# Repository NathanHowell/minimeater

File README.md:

# minimeater

A fan controller for a Big Green Egg Large. It is a single 3D-printed box that clips onto the egg's intake tube. It
meters air into the fire with a fan and a servo-driven flap to hold the pit at a setpoint between 150 and 325 °F.
It runs from one USB-C cable and talks to Home Assistant over MQTT.

> [!WARNING]
> **Status: design, not yet built.** The board, the enclosure and the firmware are complete enough to order and run in
> simulation, but no unit has been made or used on a real cook. Expect changes, and don't trust it with a fire yet.

## What it does

- **Holds the pit temperature.** A model-predictive controller plans the airflow half an hour ahead on a model of the
  egg, because the pit answers a change of air long after it is made. It treats overshoot as much worse than
  undershoot (a kamado can only be starved of air, not cooled) and continuously estimates what the model doesn't know:
  the fire, the weather and the food. It commands airflow; the fan and the flap are scheduled to deliver it. It
  recovers from an opened lid, tunes itself during a cook and resumes after a power cut.
- **Watches the food.** Four thermistor probe jacks. Any of them can be the pit probe (it is found automatically); the
  rest report temperature, rate of rise, an estimated finish time and stall detection, with high and low alarms.
- **Fits in with a smart home.** Home Assistant entities through MQTT discovery, over TLS 1.3 with a per-device key held
  in a secure element. Metrics go to any OpenTelemetry collector. WiFi is set up from the browser (Improv) or the
  serial console.
- **Needs nothing else.** One USB-C port powers it, flashes it and carries the console. No 12 V supply, no separate
  blower.

## Safety

This device controls a fire. A fault in the controller, the firmware or the setup can leave the fan running and the
pit far hotter than intended. Use it only on a cooker you would otherwise trust to be left alone, keep the cooker's
own vents set so that a fan running flat out is still safe, and don't leave a cook unattended until you have tested it
yourself. It comes with no warranty (see [License](#license)).

## How it is built

<p align="center"><sub>The board, 47.5 × 54 mm, four layers. It hangs parts-down in the box, so the silk side is the face you see with the case open.</sub></p>

| | Where | Docs |
|---|---|---|
| **Board** | `hw/`: KiCad 10, four layers, assembled by JLCPCB. An ESP32-C6, the probe front end, USB-C power, the fan and servo drivers, an ATECC608B for the device key | [ADRs](docs/adr/), [ICD](docs/icd.md), [ordering](docs/ordering.md) |
| **Enclosure** | `src/minimeater/mech/`: build123d, printed in MJF nylon (duct, hood, pan) with a few CNC parts (flap, crank, coupler, rod) | [mech](docs/mech.md), [JLC3DP notes](docs/jlc3dp.md), [CFD](docs/cfd.md) |
| **Firmware** | `fw/`: Rust, `no_std`, embassy. `minimeater-core` (control, food estimator, probe conversion), `minimeater-app` (the application, generic over the board), `minimeater-fw` (the ESP32-C6 binding) | [MQTT protocol](docs/protocol.md), [telemetry](docs/telemetry.md), [provisioning](docs/provisioning.md) |
| **Digital twin** | `fw/minimeater-sim` and `fw/minimeater-twin`: the real application tasks on a virtual clock against a simulated board and kamado | [sim](docs/sim/) |
| **Models** | `src/minimeater/model/`: the Python plant, airflow and controller models the firmware was ported from | [modeling](docs/modeling/) |

Decisions are recorded in [`docs/adr/`](docs/adr/). The MQTT schema in [`docs/protocol.md`](docs/protocol.md) is
normative.

## Building and testing

You need [just](https://just.systems/), [uv](https://docs.astral.sh/uv/) for the Python side and a Rust toolchain for
the firmware. Every task is a recipe, grouped by area; `just` lists them all.

```bash
just test                     # the Python suite and the firmware's host tests
just ci                       # everything CI runs, KiCad checks included
just fw::flash                # build the firmware and flash an ESP32-C6 over USB-C
```

Run a cook on the twin, or the whole scenario suite:

```bash
just fw::twin::run --scenario kamado-brisket --speed 60x
just fw::twin::scenarios      # bounds and baselines for every scenario, a plot of each
```

Regenerate the derived outputs:

```bash
just model::all               # docs/modeling and docs/sim
just mech::export             # STEP and STL of every part, ready to order (build/mech)
just mech::render             # the enclosure renders (docs/mech)
just hw::fab                  # gerbers, BOM and placement for JLCPCB (hw/fab)
just hw::renders              # the board renders above (KiCad's raytracer; needs pngquant and oxipng)
just mech::explode            # the animation above (Blender Cycles; needs img2webp)
```

The vendor 3D models of the fan, the servo and a few board parts are not redistributed here. `just vendor::fetch`
fetches or installs them. Everything builds and tests without them; a few fit checks are skipped.

Integration checks against real services run in containers, under `just fw::interop::` (`mqtt`, `tls`, `otlp`,
`ha-discovery`, and `ha-live` against a real Home Assistant). `just stack::up` starts Mosquitto and an OpenTelemetry
collector for the twin to cook against (`just fw::twin::stack`).

## Contributing

There is no public issue tracker. Pull requests are welcome: please run `just test` (or `just ci`) before sending
one, and regenerate any derived docs you touch rather than editing them by hand.

## License

Copyright (c) 2026 Nathan Howell. The hardware (`hw/` and the enclosure in `src/minimeater/mech/`) is under the
[CERN-OHL-S v2](LICENSES/CERN-OHL-S-2.0.txt). The firmware, the Python models and tools, and the docs are under the
[GPL v3 or later](LICENSES/GPL-3.0-or-later.txt), with an added permission to link the vendor's binary-only radio
libraries. [LICENSE](LICENSE) has the details and lists the third-party files that keep their own terms.

Big Green Egg is a trademark of its owner. This project is not affiliated with or endorsed by it.

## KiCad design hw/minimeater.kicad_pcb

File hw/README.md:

# hw

KiCad project for the controller board. Schematic and layout start at `.3.x`.

- **Assembly:** JLCPCB, about 5 boards. Every PCB part must be in JLC stock (check with `just hw::stock <keyword|C#>`). Where there is a choice, pick the higher-quality part unless it costs much more.
- **Inputs:** ADR 0001 (MCU and pin budget), ADR 0002 (probe front-end) and the ICD (`docs/icd.md`, `.1.2`).

## Board setup

- **Stackup:** 4 layers (F.Cu / In1.Cu GND plane / In2.Cu / B.Cu). The ground plane helps the module's antenna, USB and the buck converter. JLCPCB JLC04161H-7628, 1.6 mm, set in Board Setup: 1 oz outer (0.035), 7628 prepreg 0.2104 mm (er 4.4), 0.5 oz inner (0.0152), core 1.065 mm (er 4.6); ENIG finish (the 0.5 mm WSONs, the TSSOP and the module's pads want flat pads). Order with the same stackup and finish on JLC's form: it reads them from there, not from the file. "Mark on PCB": Remove Mark (the back silk has no order-number placeholder).
- **Rules:** min track and clearance 0.127 mm, via 0.6/0.3 mm, hole-to-hole 0.5 mm (JLCPCB 4-layer).
- **Outline:** 46 × 54 mm, 2 mm corner radius, origin at the top-left corner, +y down (46 because the USB-C and four jacks side by side need 45 mm). Three 2.7 mm mounting holes at (12.05, 28.5), (43.0, 29.8), (43.0, 49.6): the corners are taken by the connector row and the module.
- **Frame mapping:** the enclosure's frame (`just mech::envelope`, `docs/mech.md`) is centred, so KiCad (x, y) = envelope (x + 23, y + 27). The connector row on the envelope's -y edge is the top edge of the KiCad board (y = 0), with the USB-C at KiCad x = 5.7.
- **Editing:** only through the Konnect MCP tools; never edit the `.kicad_*` files by hand.
- **Assembly:** single-sided SMT at JLCPCB (cost): every SMT part on the top side. The through-hole fan and servo headers are hand-soldered. The TMP117 therefore sits on top (see the bead on the ambient vent path).
- **Placement:** done by script from the courtyard sizes (first pass; routing is next). Module at the +y end with its antenna toward the +y edge; fan and servo headers on the rear (x = 0) edge; the TMP117 at the rear +y corner; LED at x = 38 on the +y edge; three on-board fiducials; JLC adds the edge rails and tooling holes at order time.

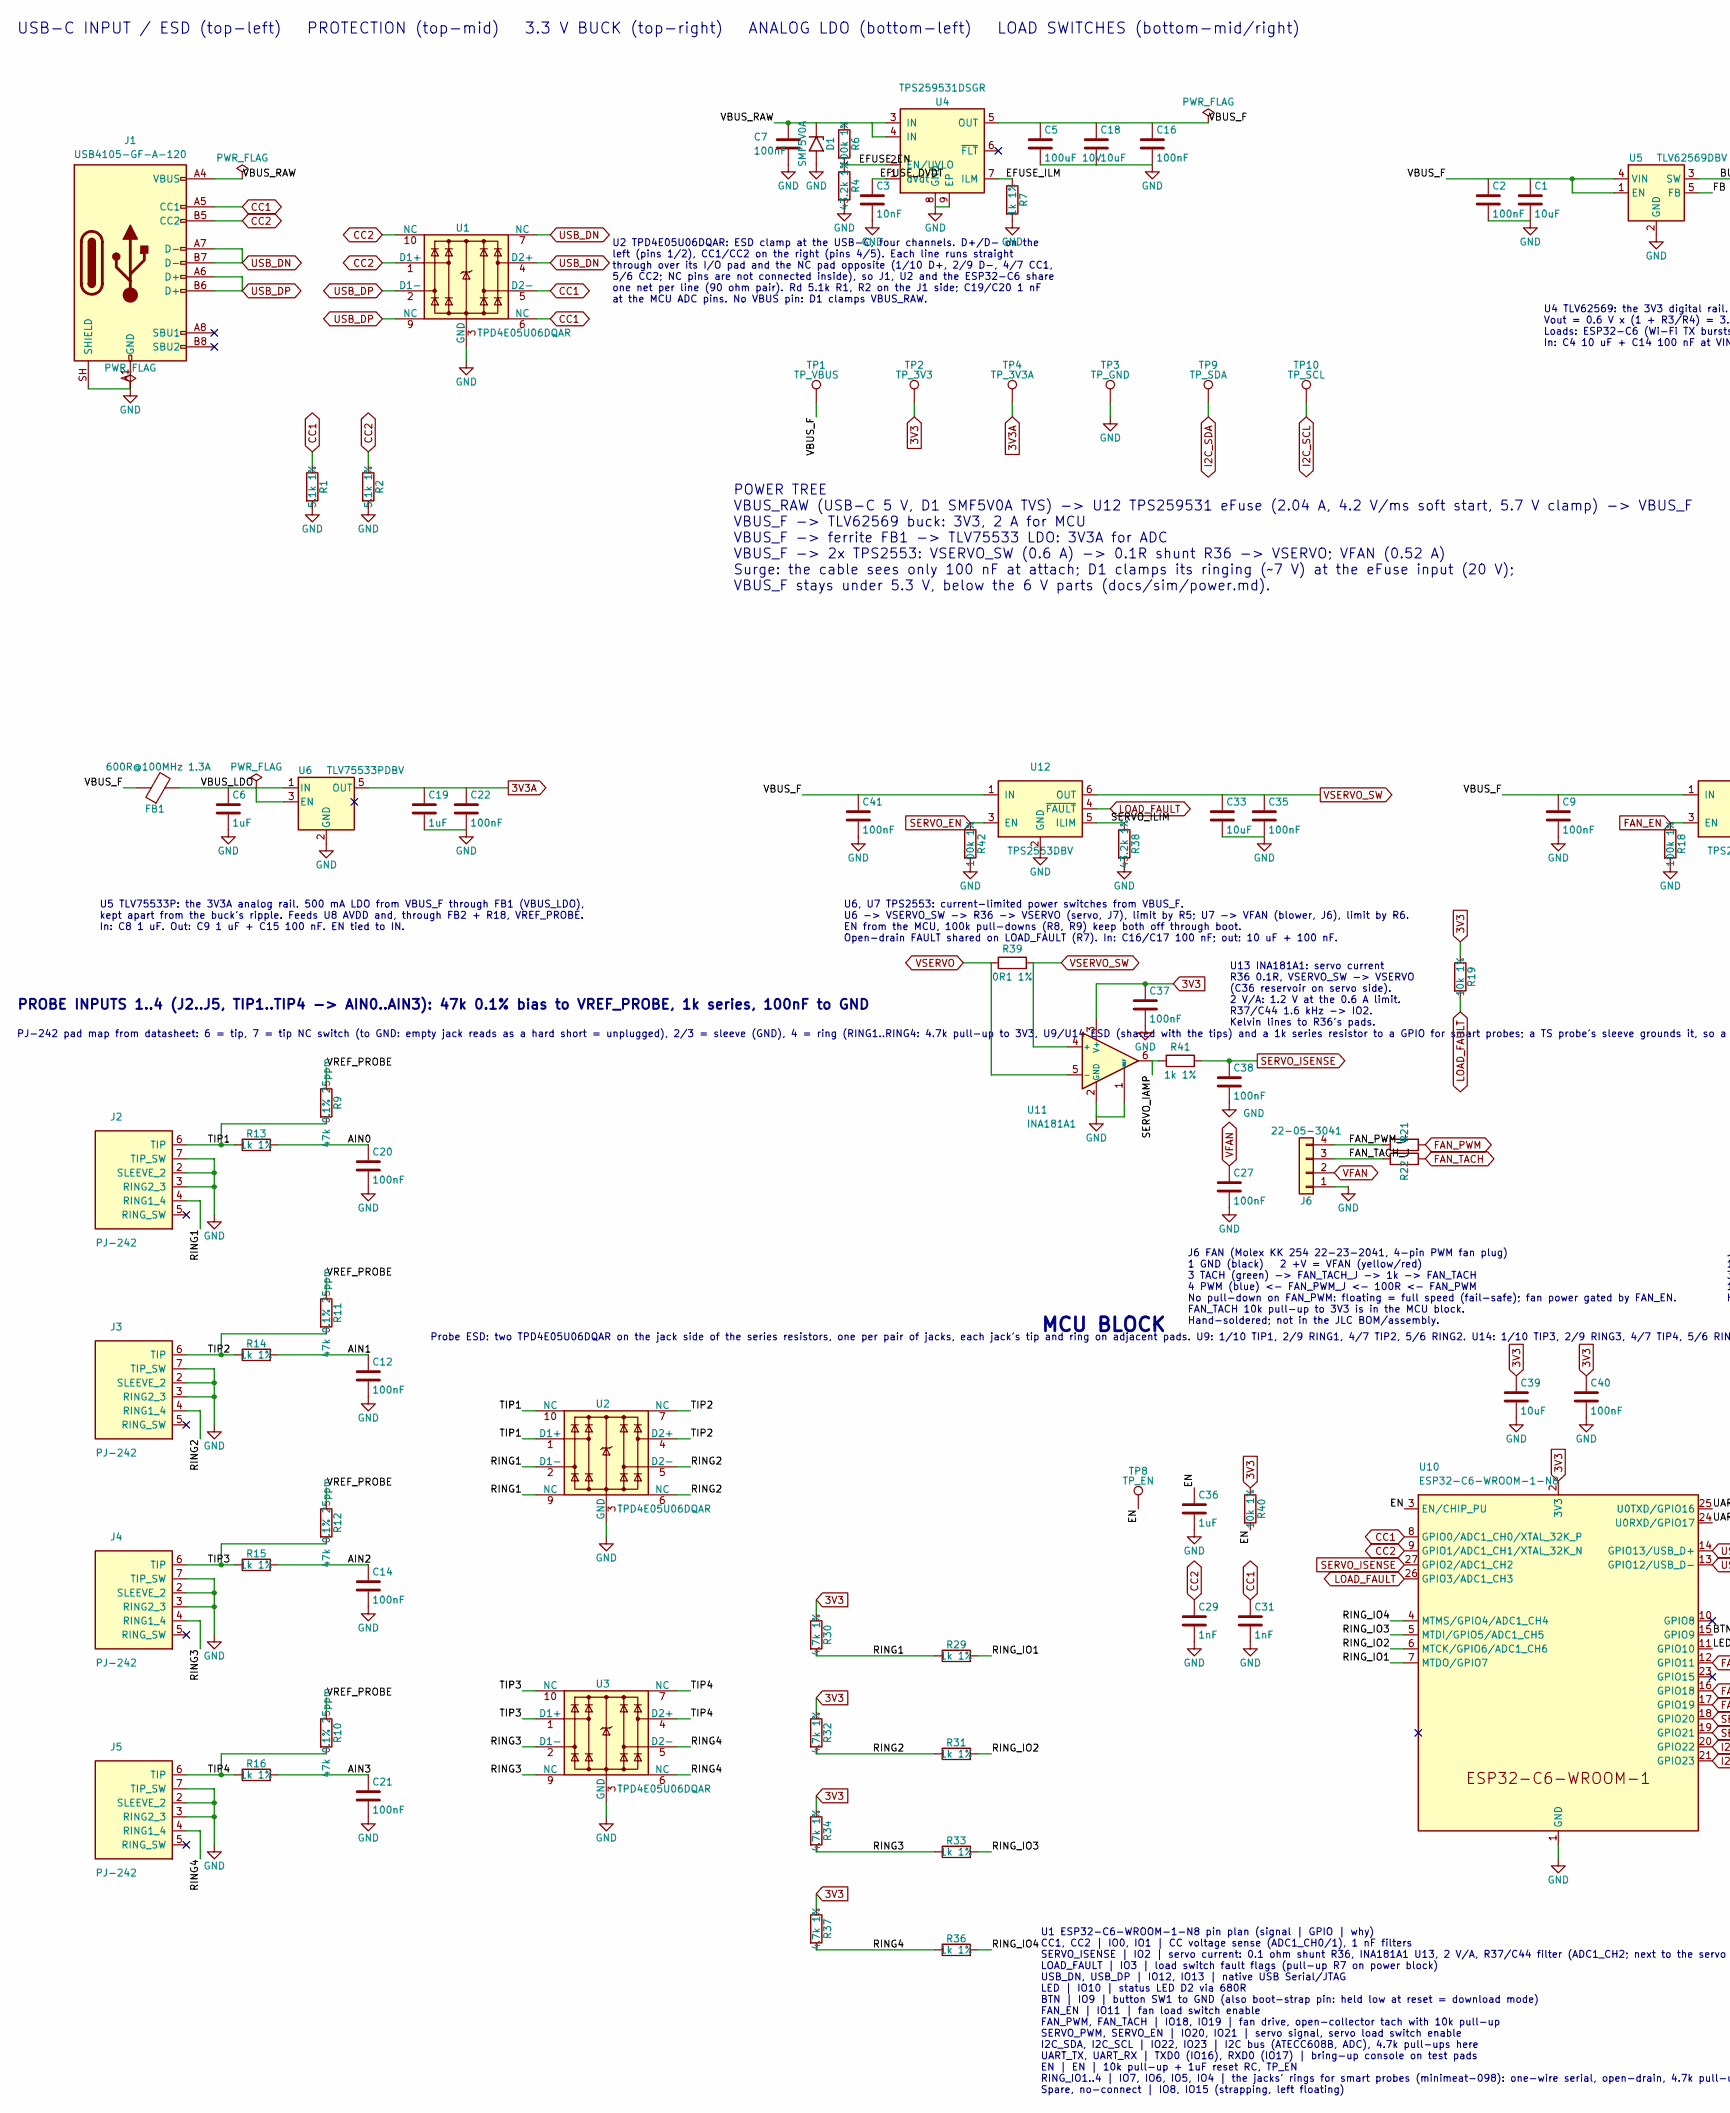
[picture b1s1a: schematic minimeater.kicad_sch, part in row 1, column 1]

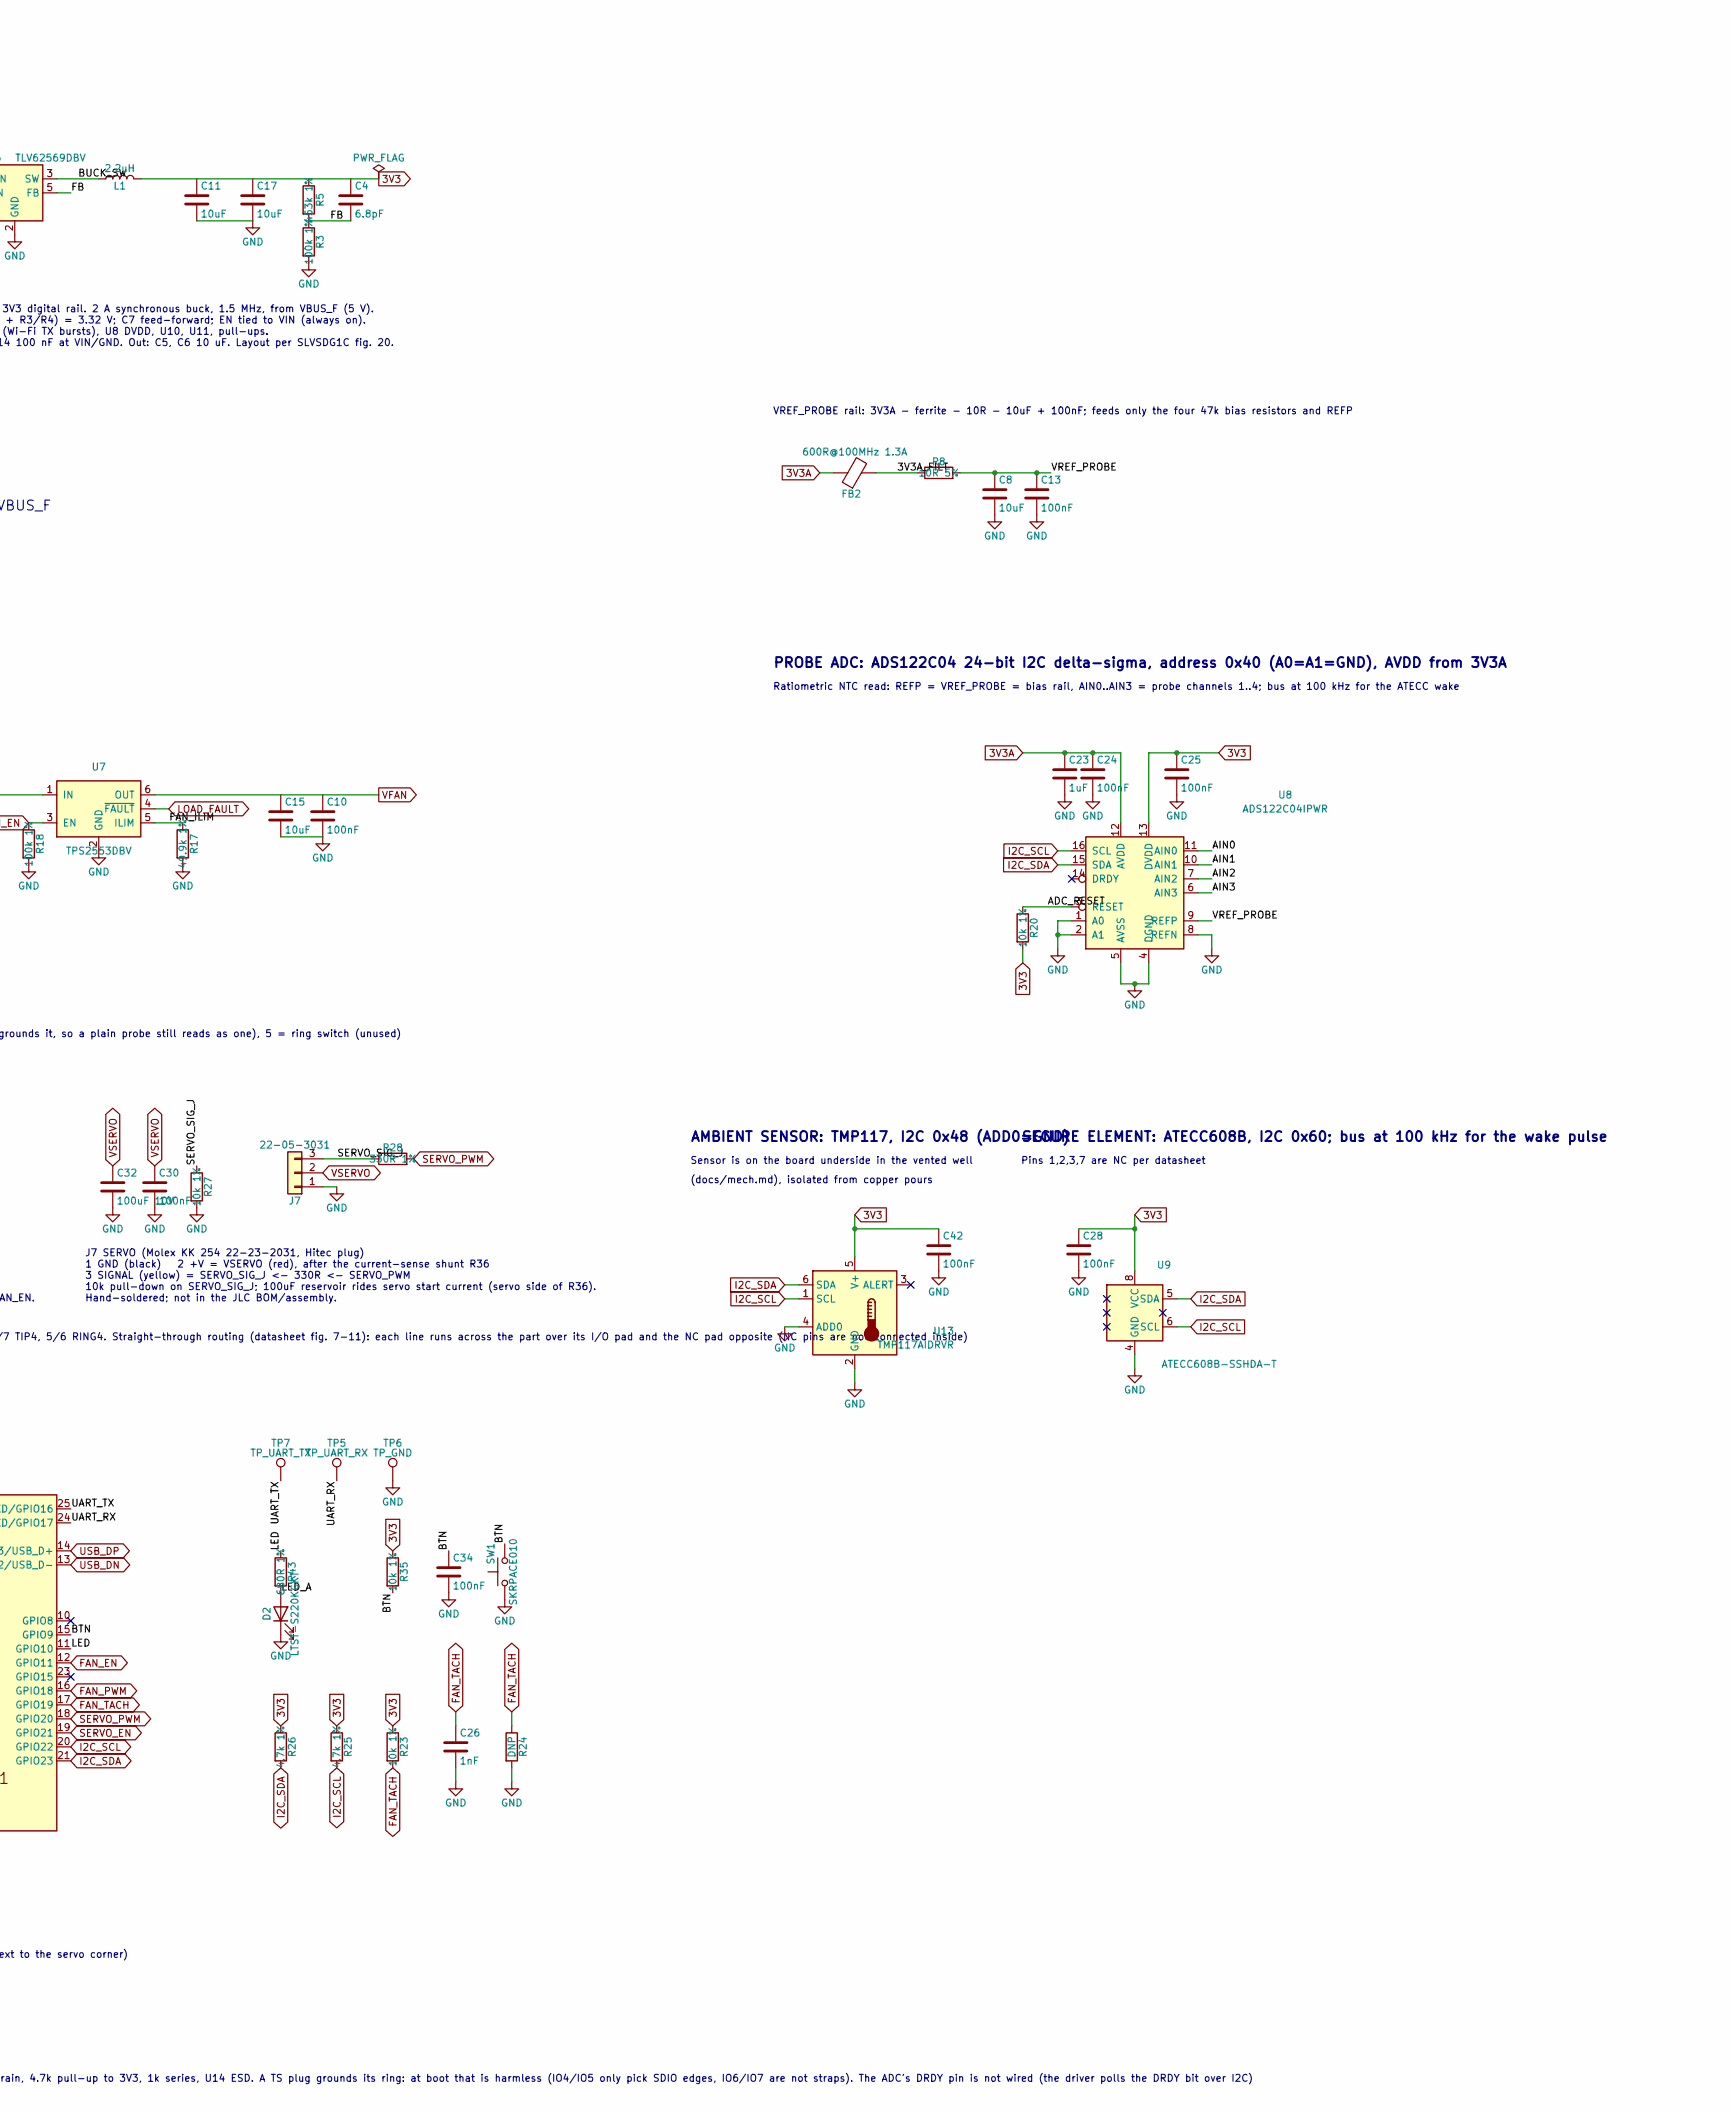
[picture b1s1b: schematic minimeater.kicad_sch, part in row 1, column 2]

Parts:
C1, C8, C11, C15, C17, C18, C33, C39: 10uF; C_0805_2012Metric; MPN CL21A106KAYNNNE; LCSC C15850
C2, C7, C9, C10, C12, C13, C14, C16, C20, C21, C22, C24, C25, C27, C28, C30, C34, C35, C37, C38, C40, C41, C42: 100nF; C_0402_1005Metric; MPN CL05B104KO5NNNC; LCSC C1525
C3: 10nF; C_0402_1005Metric; MPN CL05B103KB5NNNC; LCSC C15195
C4: 6.8pF; C_0402_1005Metric; MPN CL05C6R8CB5NNNC; LCSC C318598
C5, C32: 100uF 10V; C_1210_3225Metric; MPN CL32A107MPVNNNE; LCSC C23742
C6, C19, C23, C36: 1uF; C_0402_1005Metric; MPN CL05A105KA5NQNC; LCSC C52923
C26, C29, C31: 1nF; C_0402_1005Metric; MPN 0402B102K500NT; LCSC C1523
D1: SMF5V0A; D_SMF; MPN SMF5.0A; LCSC C151296
D2: LTST-S220KGKT; MPN LTST-S220KGKT; LCSC C160469
FB1: 600R@100MHz 1.3A; L_0603_1608Metric; LCSC C85833
FB2: 600R@100MHz 1.3A; L_0603_1608Metric; MPN BLM18KG601SN1D; LCSC C85833
J1: USB4105-GF-A-120; USB_C_Receptacle_GCT_USB4105-xx-A_16P_TopMnt_Horizontal; MPN USB4105-GF-A-120; LCSC C5184243
J2, J3, J4, J5: PJ-242; MPN PJ-242; LCSC C431536
J6: 22-05-3041; KK254-RA-04; LCSC N/A hand-solder (Mouser/Digi-Key 22-05-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
J7: 22-05-3031; KK254-RA-03; LCSC N/A hand-solder (Mouser/Digi-Key 22-05-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
L1: 2.2uH; LQH3NPN2R2MMEL; MPN LQH3NPN2R2MMEL; LCSC C668451
R1, R2: 5.1k 1%; R_0402_1005Metric; MPN RC0402FR-075K1L; LCSC C105872
R3, R6, R18, R42: 100k 1%; R_0402_1005Metric; MPN RC0402FR-07100KL; LCSC C60491
R4, R38: 43.2k 1%; R_0402_1005Metric; MPN RC0402FR-0743K2L; LCSC C137980
R5: 453k 1%; R_0402_1005Metric; MPN 0402WGF4533TCE; LCSC C27009
R7, R13, R14, R15, R16, R22, R29, R31, R33, R36, R41: 1k 1%; R_0402_1005Metric; MPN 0402WGF1001TCE; LCSC C11702
R8: 10R 5%; R_0402_1005Metric; MPN 0402WGF100JTCE; LCSC C25077
R9, R10, R11, R12: 47k 0.1% 25ppm; R_0603_1608Metric; MPN TNPW060347K0BEEA; LCSC C2089026
R17: 49.9k 1%; R_0402_1005Metric; MPN RC0402FR-0749K9L; LCSC C137969
R19, R20, R23, R27, R35, R40: 10k 1%; R_0402_1005Metric; MPN RC0402FR-0710KL; LCSC C60490
R21: 100R 1%; R_0402_1005Metric; MPN 0402WGF1000TCE; LCSC C25076
R24: DNP; R_0402_1005Metric; LCSC DNP: rework only (FAN_TACH divider if t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
R25, R26, R30, R32, R34, R37: 4.7k 1%; R_0402_1005Metric; MPN 0402WGF4701TCE; LCSC C25900
R28: 330R 1%; R_0402_1005Metric; MPN 0402WGF3300TCE; LCSC C25104
R39: 0R1 1%; R_0402_1005Metric; MPN ERJ-2BWFR100X; LCSC C2088598
R43: 680R 1%; R_0402_1005Metric; MPN RC0402FR-07680RL; LCSC C137948
SW1: SKRPACE010; MPN SKRPACE010; LCSC C139797
TP1: TP_VBUS; TestPoint_Pad_D1.5mm; LCSC N/A (not assembled)
TP2: TP_3V3; TestPoint_Pad_D1.5mm; LCSC N/A (not assembled)
TP3, TP6: TP_GND; TestPoint_Pad_1.5x1.5mm; LCSC N/A (not assembled)
TP4: TP_3V3A; TestPoint_Pad_D1.5mm; LCSC N/A (not assembled)
TP5: TP_UART_RX; TestPoint_Pad_D1.5mm; LCSC N/A (not assembled)
TP7: TP_UART_TX; TestPoint_Pad_D1.5mm; LCSC N/A (not assembled)
TP8: TP_EN; TestPoint_Pad_D1.5mm; LCSC N/A (not assembled)
TP9: TP_SDA; TestPoint_Pad_D1.5mm; LCSC N/A (not assembled)
TP10: TP_SCL; TestPoint_Pad_D1.5mm; LCSC N/A (not assembled)
U1, U2, U3: TPD4E05U06DQAR; TPD4E05U06DQA; MPN TPD4E05U06DQAR; LCSC C138714
U4: TPS259531DSGR; Texas_DSG0008A_WSON-8-1EP_2x2mm_P0.5mm_EP0.9x1.6mm; MPN TPS259531DSGR; LCSC C2155674
U5: TLV62569DBV; SOT-23-5; MPN TLV62569DBVR; LCSC C141836
U6: TLV75533PDBV; SOT-23-5; MPN TLV75533PDBVR; LCSC C404027
U7, U12: TPS2553DBV; SOT-23-6; MPN TPS2553DBVR; LCSC C55266
U8: ADS122C04IPWR; TSSOP-16_4.4x5mm_P0.65mm; MPN ADS122C04IPWR; LCSC C2872338
U9: ATECC608B-SSHDA-T; SOIC-8_3.9x4.9mm_P1.27mm; MPN ATECC608B-SSHDA-T; LCSC C1518769
U10: ESP32-C6-WROOM-1-N8; ESP32-C6-WROOM-1; MPN ESP32-C6-WROOM-1-N8; LCSC C5366877
U11: INA181A1; SOT-363_SC-70-6; MPN INA181A1IDCKR; LCSC C22443503
U13: TMP117AIDRVR; TMP117AIDRV_WSON-6_noEP; MPN TMP117AIDRVR; LCSC C699536

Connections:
3V3A: C19.1, C22.1, C23.1, C24.1, FB2.1, TP4.1 (1_1), U6.5 (OUT), U8.12 (AVDD)
/3V3A_FILT: FB2.2, R8.1
/ADC_RESET: R20.1, U8.3 (RESET)
/AIN0: C20.1, R13.2, U8.11 (AIN0)
/AIN1: C12.1, R14.2, U8.10 (AIN1)
/AIN2: C14.1, R15.2, U8.7 (AIN2)
/AIN3: C21.1, R16.2, U8.6 (AIN3)
/BTN: C34.1, R35.2, SW1.2, U10.15 (GPIO9)
/BUCK_SW: L1.1, U5.3 (SW)
/EFUSE_DVDT: C3.1, U4.1 (dVdt)
/EFUSE_EN: R4.1, R6.2, U4.2 (EN/UVLO)
/EFUSE_ILM: R7.1, U4.7 (ILM)
/EN: C36.1, R40.2, TP8.1 (1_1), U10.3 (EN/CHIP_PU)
/FAN_ILIM: R17.1, U7.5 (ILIM)
/FAN_PWM_J: J6.4, R21.1
/FAN_TACH_J: J6.3, R22.1
/FB: C4.2, R3.1, R5.2, U5.5 (FB)
/LED: R43.1, U10.11 (GPIO10)
/LED_A: D2.2 (A), R43.2
/RING1: J2.4 (RING1_4), R29.1, R30.2, U2.2 (D1-), U2.9 (NC)
/RING2: J3.4 (RING1_4), R31.1, R32.2, U2.5 (D2-), U2.6 (NC)
/RING3: J4.4 (RING1_4), R33.1, R34.2, U3.2 (D1-), U3.9 (NC)
/RING4: J5.4 (RING1_4), R36.1, R37.2, U3.5 (D2-), U3.6 (NC)
/RING_IO1: R29.2, U10.7 (MTDO/GPIO7)
/RING_IO2: R31.2, U10.6 (MTCK/GPIO6/ADC1_CH6)
/RING_IO3: R33.2, U10.5 (MTDI/GPIO5/ADC1_CH5)
/RING_IO4: R36.2, U10.4 (MTMS/GPIO4/ADC1_CH4)
/SERVO_IAMP: R41.1, U11.6
/SERVO_ILIM: R38.1, U12.5 (ILIM)
/SERVO_SIG_J: J7.3, R27.1, R28.1
/TIP1: J2.6 (TIP), R9.2, R13.1, U2.1 (D1+), U2.10 (NC)
/TIP2: J3.6 (TIP), R11.2, R14.1, U2.4 (D2+), U2.7 (NC)
/TIP3: J4.6 (TIP), R12.2, R15.1, U3.1 (D1+), U3.10 (NC)
/TIP4: J5.6 (TIP), R10.2, R16.1, U3.4 (D2+), U3.7 (NC)
/UART_RX: TP5.1 (1_1), U10.24 (U0RXD/GPIO17)
/UART_TX: TP7.1 (1_1), U10.25 (U0TXD/GPIO16)
/VREF_PROBE: C8.1, C13.1, R8.2, R9.1, R10.1, R11.1, R12.1, U8.9 (REFP)
CC1: C31.1, J1.A5 (CC1), R1.1, U1.5 (D2-), U1.6 (NC), U10.8 (GPIO0/ADC1_CH0/XTAL_32K_P)
CC2: C29.1, J1.B5 (CC2), R2.1, U1.1 (D1+), U1.10 (NC), U10.9 (GPIO1/ADC1_CH1/XTAL_32K_N)
FAN_EN: R18.1, U7.3 (EN), U10.12 (GPIO11)
FAN_PWM: R21.2, U10.16 (GPIO18)
FAN_TACH: C26.1, R22.2, R23.2, R24.1, U10.17 (GPIO19)
I2C_SCL: R25.2, TP10.1 (1_1), U8.16 (SCL), U9.6 (SCL), U10.20 (GPIO22), U13.1 (SCL)
I2C_SDA: R26.2, TP9.1 (1_1), U8.15 (SDA), U9.5 (SDA), U10.21 (GPIO23), U13.6 (SDA)
LOAD_FAULT: R19.2, U7.4 (~FAULT), U10.26 (GPIO3/ADC1_CH3), U12.4 (~FAULT)
SERVO_EN: R42.1, U10.19 (GPIO21), U12.3 (EN)
SERVO_ISENSE: C38.1, R41.2, U10.27 (GPIO2/ADC1_CH2)
SERVO_PWM: R28.2, U10.18 (GPIO20)
USB_DN: J1.A7 (D-), J1.B7 (D-), U1.4 (D2+), U1.7 (NC), U10.13 (GPIO12/USB_D-)
USB_DP: J1.A6 (D+), J1.B6 (D+), U1.2 (D1-), U1.9 (NC), U10.14 (GPIO13/USB_D+)
VFAN: C10.1, C15.1, C27.1, J6.2, U7.6 (OUT)
VSERVO: C30.1, C32.1, J7.2, R39.1, U11.5 (-)
VSERVO_SW: C33.1, C35.1, R39.2, U11.4 (+), U12.6 (OUT)

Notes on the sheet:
MCU BLOCK
Ratiometric NTC read: REFP = VREF_PROBE = bias rail, AIN0..AIN3 = probe channels 1..4; bus at 100 kHz for the ATECC wake
AMBIENT SENSOR: TMP117, I2C 0x48 (ADD0=GND)
U4 TLV62569: the 3V3 digital rail. 2 A synchronous buck, 1.5 MHz, from VBUS_F (5 V). Vout = 0.6 V x (1 + R3/R4) = 3.32 V; C7 feed-forward; EN tied to VIN (always on). Loads: ESP32-C6 (Wi-Fi TX bursts), U8 DVDD, U10, U11, pull-ups. In: C4 10 uF + C14 100 nF at VIN/GND. Out: C5, C6 10 uF. Layout per 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
Sensor is on the board underside in the vented well
PROBE INPUTS 1..4 (J2..J5, TIP1..TIP4 -> AIN0..AIN3): 47k 0.1% bias to VREF_PROBE, 1k series, 100nF to GND
Pins 1,2,3,7 are NC per datasheet
U13 INA181A1: servo current R36 0.1R, VSERVO_SW -> VSERVO (C36 reservoir on servo side). 2 V/A: 1.2 V at the 0.6 A limit. R37/C44 1.6 kHz -> IO2. Kelvin lines to R36's pads.
J6 FAN (Molex KK 254 22-23-2041, 4-pin PWM fan plug) 1 GND (black) 2 +V = VFAN (yellow/red) 3 TACH (green) -> FAN_TACH_J -> 1k -> FAN_TACH 4 PWM (blue) <- FAN_PWM_J <- 100R <- FAN_PWM No pull-down on FAN_PWM: floating = full speed (fail-safe); fan power gated by FAN_EN. FAN_TACH 10k pull-up to 3V3 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
Probe ESD: two TPD4E05U06DQAR on the jack side of the series resistors, one per pair of jacks, each jack's tip and ring on adjacent pads. U9: 1/10 TIP1, 2/9 RING1, 4/7 TIP2, 5/6 RING2. U14: 1/10 TIP3, 2/9 RING3, 4/7 TIP4, 5/6 RING4. Straight-through routing (datasheet fig. 7-11): each line runs acr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
U6, U7 TPS2553: current-limited power switches from VBUS_F. U6 -> VSERVO_SW -> R36 -> VSERVO (servo, J7), limit by R5; U7 -> VFAN (blower, J6), limit by R6. EN from the MCU, 100k pull-downs (R8, R9) keep both off through boot. Open-drain FAULT shared on LOAD_FAULT (R7). In: C16/C17 100 nF; out: 10 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
POWER TREE VBUS_RAW (USB-C 5 V, D1 SMF5V0A TVS) -> U12 TPS259531 eFuse (2.04 A, 4.2 V/ms soft start, 5.7 V clamp) -> VBUS_F VBUS_F -> TLV62569 buck: 3V3, 2 A for MCU VBUS_F -> ferrite FB1 -> TLV75533 LDO: 3V3A for ADC VBUS_F -> 2x TPS2553: VSERVO_SW (0.6 A) -> 0.1R shunt R36 -> VSERVO; VFAN (0.52 A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
USB-C INPUT / ESD (top-left) PROTECTION (top-mid) 3.3 V BUCK (top-right) ANALOG LDO (bottom-left) LOAD SWITCHES (bottom-mid/right)
(docs/mech.md), isolated from copper pours
U2 TPD4E05U06DQAR: ESD clamp at the USB-C, four channels. D+/D- on the left (pins 1/2), CC1/CC2 on the right (pins 4/5). Each line runs straight through over its I/O pad and the NC pad opposite (1/10 D+, 2/9 D-, 4/7 CC1, 5/6 CC2; NC pins are not connected inside), so J1, U2 and the ESP32-C6 share o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
PROBE ADC: ADS122C04 24-bit I2C delta-sigma, address 0x40 (A0=A1=GND), AVDD from 3V3A
SECURE ELEMENT: ATECC608B, I2C 0x60; bus at 100 kHz for the wake pulse
J7 SERVO (Molex KK 254 22-23-2031, Hitec plug) 1 GND (black) 2 +V = VSERVO (red), after the current-sense shunt R36 3 SIGNAL (yellow) = SERVO_SIG_J <- 330R <- SERVO_PWM 10k pull-down on SERVO_SIG_J; 100uF reservoir rides servo start current (servo side of R36). Hand-soldered; not in the JLC BOM/ass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
PJ-242 pad map from datasheet: 6 = tip, 7 = tip NC switch (to GND: empty jack reads as a hard short = unplugged), 2/3 = sleeve (GND), 4 = ring (RING1..RING4: 4.7k pull-up to 3V3, U9/U14 ESD (shared with the tips) and a 1k series resistor to a GPIO for smart probes; a TS probe's sleeve grounds it, s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
U5 TLV75533P: the 3V3A analog rail. 500 mA LDO from VBUS_F through FB1 (VBUS_LDO), kept apart from the buck's ripple. Feeds U8 AVDD and, through FB2 + R18, VREF_PROBE. In: C8 1 uF. Out: C9 1 uF + C15 100 nF. EN tied to IN.
U1 ESP32-C6-WROOM-1-N8 pin plan (signal | GPIO | why) CC1, CC2 | IO0, IO1 | CC voltage sense (ADC1_CH0/1), 1 nF filters SERVO_ISENSE | IO2 | servo current: 0.1 ohm shunt R36, INA181A1 U13, 2 V/A, R37/C44 filter (ADC1_CH2; next to the servo corner) LOAD_FAULT | IO3 | load switch fault flags (pull-up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
VREF_PROBE rail: 3V3A - ferrite - 10R - 10uF + 100nF; feeds only the four 47k bias resistors and REFP

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
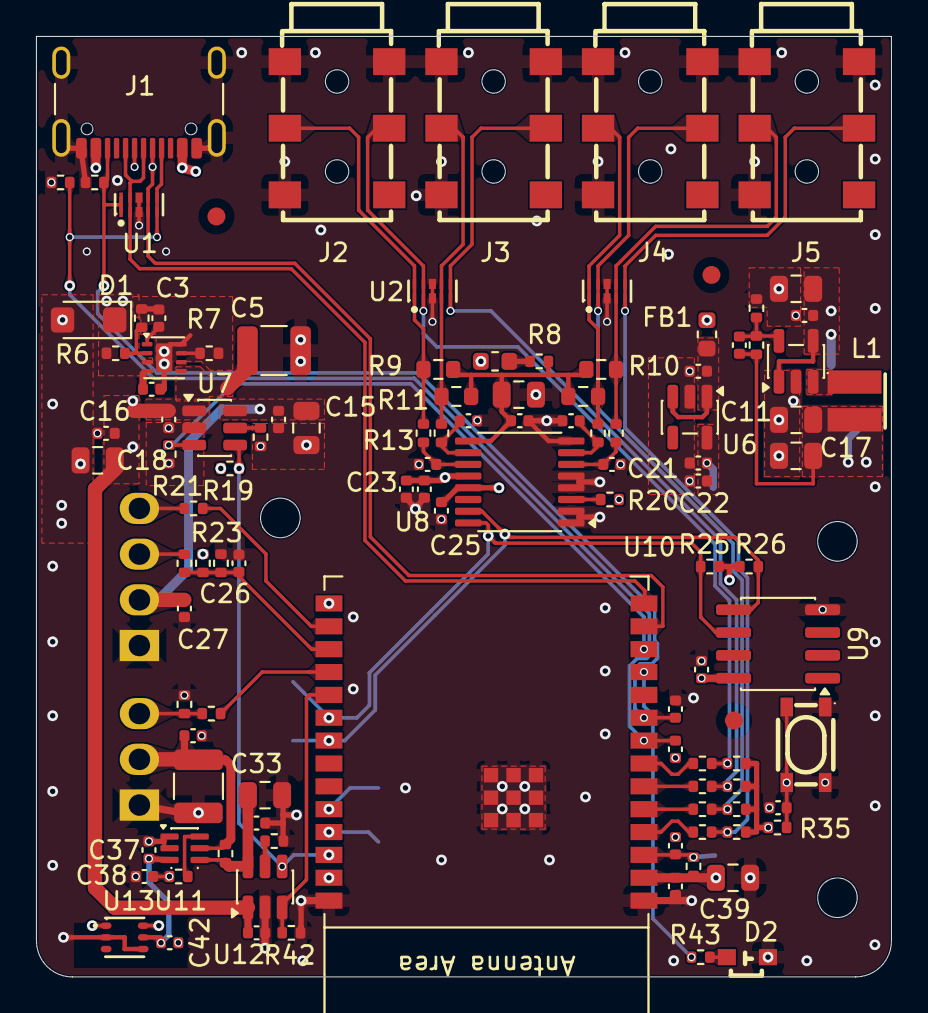
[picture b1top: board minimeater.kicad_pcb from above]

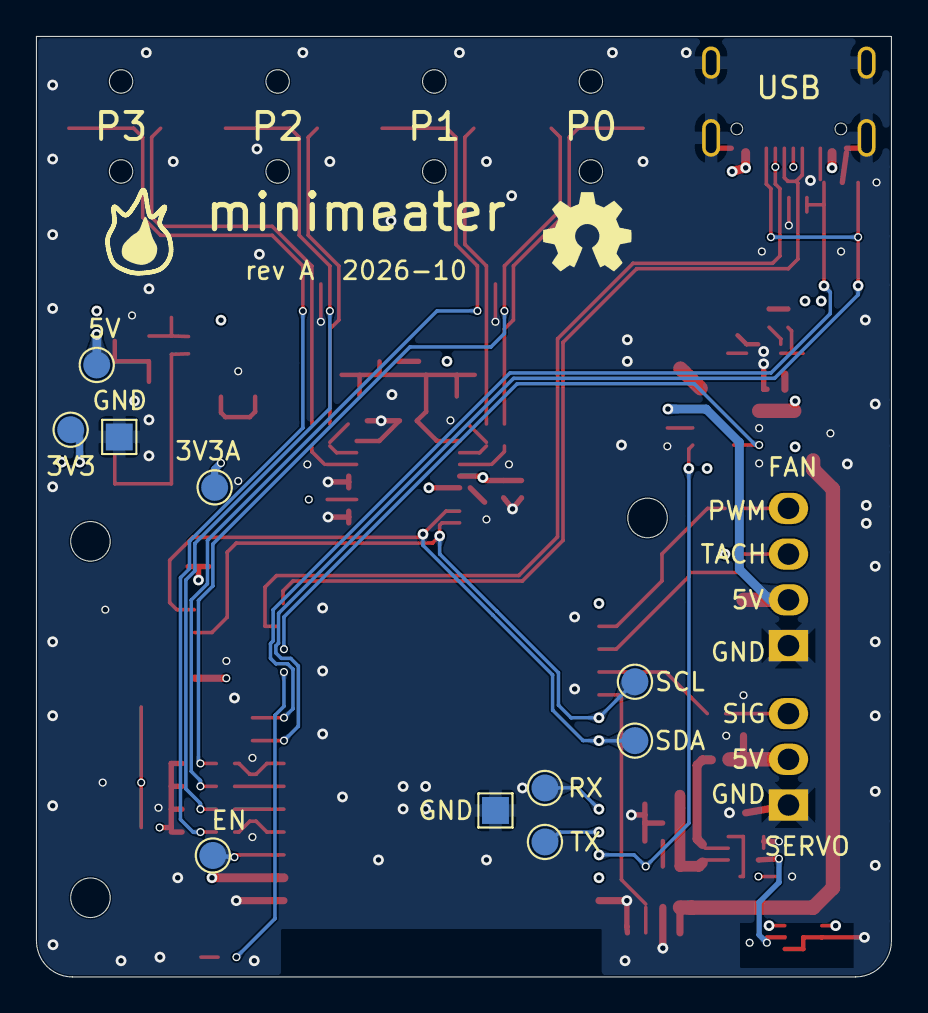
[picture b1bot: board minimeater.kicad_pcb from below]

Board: 4 copper layers, 47.5 x 52.2 mm, 127 parts (10 on the bottom side), 58 nets.

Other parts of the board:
FID1, FID2, FID3: Fiducial_1mm_Mask2mm
H1, H2, H3: MountingHole_2.2mm_M2

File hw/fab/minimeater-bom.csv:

Comment,Designator,Footprint,LCSC Part #
10uF,C1 C8 C11 C15 C17 C18 C33 C39,C_0805_2012Metric,C15850
100nF,C2 C7 C9 C10 C12 C13 C14 C16 C20 C21 C22 C24 C25 C27 C28 C30 C34 C35 C37 C38 C40 C41 C42,C_0402_1005Metric,C1525
10nF,C3,C_0402_1005Metric,C15195
6.8pF,C4,C_0402_1005Metric,C318598
100uF 10V,C5 C32,C_1210_3225Metric,C23742
1uF,C6 C19 C23 C36,C_0402_1005Metric,C52923
1nF,C26 C29 C31,C_0402_1005Metric,C1523
SMF5V0A,D1,D_SMF,C151296
LTST-S220KGKT,D2,LTST-S220KGKT,C160469
600R@100MHz 1.3A,FB1 FB2,L_0603_1608Metric,C85833
USB4105-GF-A-120,J1,USB_C_Receptacle_GCT_USB4105-xx-A_16P_TopMnt_Horizontal,C5184243
PJ-242,J2 J3 J4 J5,PJ-242,C431536
2.2uH,L1,LQH3NPN2R2MMEL,C668451
5.1k 1%,R1 R2,R_0402_1005Metric,C105872
100k 1%,R3 R6 R18 R42,R_0402_1005Metric,C60491
43.2k 1%,R4 R38,R_0402_1005Metric,C137980
453k 1%,R5,R_0402_1005Metric,C27009
1k 1%,R7 R13 R14 R15 R16 R22 R29 R31 R33 R36 R41,R_0402_1005Metric,C11702
10R 5%,R8,R_0402_1005Metric,C25077
47k 0.1% 25ppm,R9 R10 R11 R12,R_0603_1608Metric,C2089026
49.9k 1%,R17,R_0402_1005Metric,C137969
10k 1%,R19 R20 R23 R27 R35 R40,R_0402_1005Metric,C60490
100R 1%,R21,R_0402_1005Metric,C25076
4.7k 1%,R25 R26 R30 R32 R34 R37,R_0402_1005Metric,C25900
330R 1%,R28,R_0402_1005Metric,C25104
0R1 1%,R39,R_0402_1005Metric,C2088598
680R 1%,R43,R_0402_1005Metric,C137948
SKRPACE010,SW1,SKRPACE010,C139797
TPD4E05U06DQAR,U1 U2 U3,TPD4E05U06DQA,C138714
TPS259531DSGR,U4,Texas_DSG0008A_WSON-8-1EP_2x2mm_P0.5mm_EP0.9x1.6mm,C2155674
TLV62569DBV,U5,SOT-23-5,C141836
TLV75533PDBV,U6,SOT-23-5,C404027
TPS2553DBV,U7 U12,SOT-23-6,C55266
ADS122C04IPWR,U8,TSSOP-16_4.4x5mm_P0.65mm,C2872338
ATECC608B-SSHDA-T,U9,SOIC-8_3.9x4.9mm_P1.27mm,C1518769
ESP32-C6-WROOM-1-N8,U10,ESP32-C6-WROOM-1,C5366877
INA181A1,U11,SOT-363_SC-70-6,C22443503
TMP117AIDRVR,U13,TMP117AIDRV_WSON-6_noEP,C699536
